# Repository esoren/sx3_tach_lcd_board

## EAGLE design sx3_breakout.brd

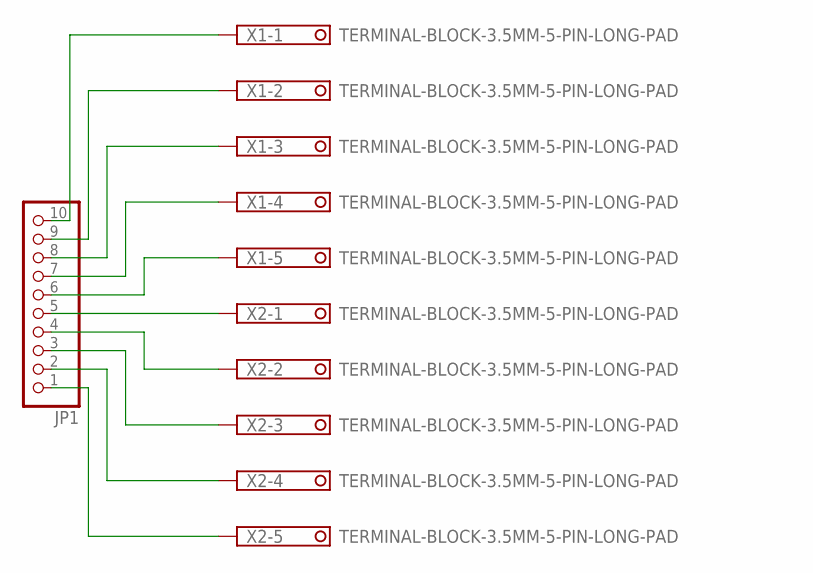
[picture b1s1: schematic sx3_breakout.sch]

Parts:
JP1: PINHD-1X10; 1X10
X1, X2: TERMINAL-BLOCK-3.5MM-5-PIN-LONG-PAD; TERMINAL-BLOCK-5-PIN-3.5MM-LONG-PAD

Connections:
unnamed: JP1.10, X1.1
unnamed: JP1.9, X1.2
unnamed: JP1.8, X1.3
unnamed: JP1.7, X1.4
unnamed: JP1.6, X1.5
unnamed: JP1.5, X2.1
unnamed: JP1.4, X2.2
unnamed: JP1.3, X2.3
unnamed: JP1.2, X2.4
unnamed: JP1.1, X2.5

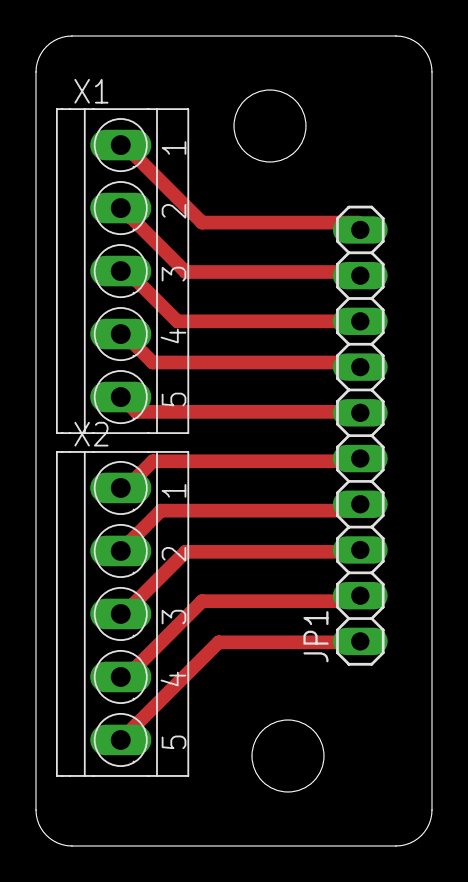
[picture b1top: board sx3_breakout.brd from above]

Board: 2 copper layers, 22.0 x 45.0 mm, 3 parts (0 on the bottom side), 10 nets.

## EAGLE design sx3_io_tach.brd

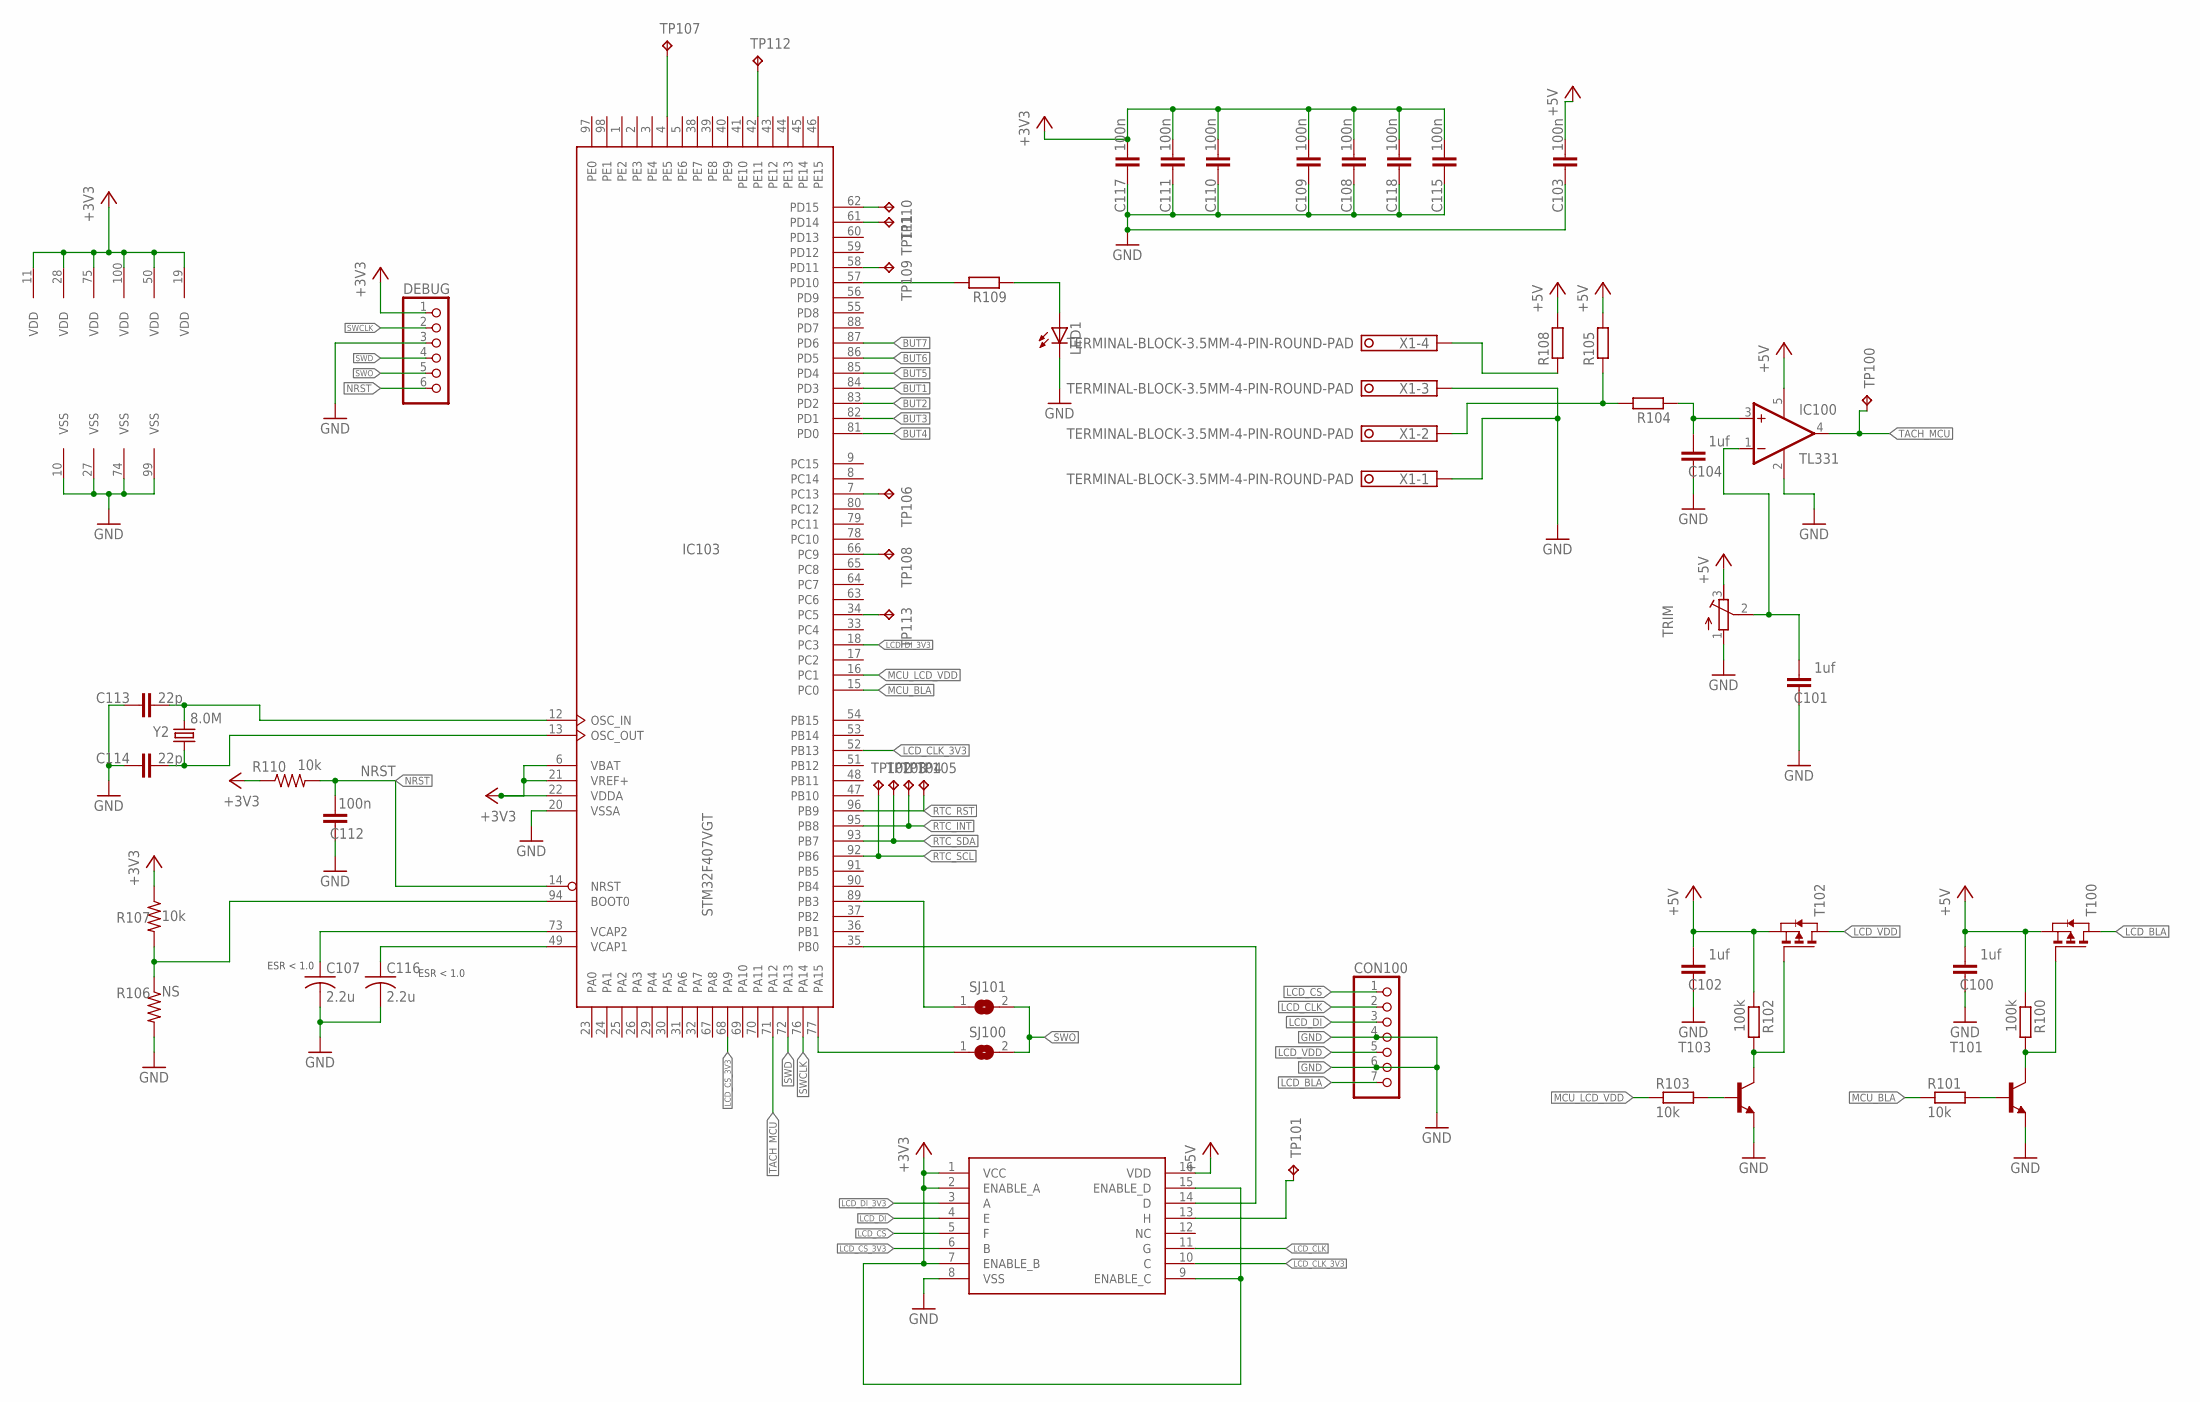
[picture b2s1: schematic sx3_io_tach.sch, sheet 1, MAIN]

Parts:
C100, C101, C102, C104: 1uf; C0603K
C103, C108, C109, C110, C111, C112, C115, C117, C118: 100n; C0603K
C107, C116: 2.2u; C1206
C113, C114: 22p; C0603K
CON100: PINHD-1X7; 1X07
DEBUG: PINHD-1X6; 1X06
IC100: TL331; DBV-R-PDSO-G5
IC103: STM32F407VGT; LQFP100
LED1: LED_ELD260; LED_LD260
R100, R102: 100k; R0603
R101, R103, R107, R110: 10k; R0603
R104, R105, R108, R109: R-EU_R0603; R0603
R106: NS; R0603
SJ100, SJ101: SJ
T100, T102: PMOSSOT23; SOT-23
T101, T103: BC817-NPN-SOT23-BEC; SOT23-BEC
TP100, TP101: TPB1,27; B1,27
TP102, TP103, TP104, TP105, TP106, TP107, TP108, TP109, TP110, TP111, TP112, TP113: TPTP17R; TP17R
TRIM: R-TRIMM3296W; RTRIM3296W
U$100: CD40109BPWR; TSSOP16
X1: TERMINAL-BLOCK-3.5MM-4-PIN-ROUND-PAD; TERMINAL-BLOCK-4-PIN-3.5MM-ROUND-PAD
Y2: 8.0M; HC49U-V

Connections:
+3V3: C108.2, C109.2, C110.2, C111.2, C115.2, C117.2, C118.2, DEBUG.1, IC103.6 (VBAT), IC103.11 (VDD), IC103.19 (VDD), IC103.21 (VREF+), IC103.22 (VDDA), IC103.28 (VDD), IC103.50 (VDD), IC103.75 (VDD), IC103.100 (VDD), R107.1, R110.1, U$100.1 (VCC), U$100.2 (ENABLE_A), U$100.7 (ENABLE_B), U$100.9 (ENABLE_C), U$100.15 (ENABLE_D); also elsewhere on the board
+5V: C100.2, C102.2, C103.2, IC100.5 (V+), R100.1, R102.1, R105.2, R108.2, T100.2 (S), T102.2 (S), TRIM.3 (E), U$100.16 (VDD); also elsewhere on the board
BOOT0: IC103.94 (BOOT0), R106.1, R107.2
BUT1: IC103.84 (PD3); also elsewhere on the board
BUT2: IC103.83 (PD2); also elsewhere on the board
BUT3: IC103.82 (PD1); also elsewhere on the board
BUT4: IC103.81 (PD0); also elsewhere on the board
BUT5: IC103.85 (PD4); also elsewhere on the board
BUT6: IC103.86 (PD5); also elsewhere on the board
BUT7: IC103.87 (PD6); also elsewhere on the board
GND: C100.1, C101.1, C102.1, C103.1, C104.1, C107.2, C108.1, C109.1, C110.1, C111.1, C112.1, C113.1, C114.1, C115.1, C116.2, C117.1, C118.1, CON100.4, CON100.6, DEBUG.3, IC100.2 (GND), IC103.10 (VSS), IC103.20 (VSSA), IC103.27 (VSS), IC103.74 (VSS), IC103.99 (VSS), LED1.K (C), R106.2, T101.E, T103.E, TRIM.1 (A), U$100.8 (VSS), X1.1, X1.3; also elsewhere on the board
LCD_BLA: CON100.7, T100.1 (D)
LCD_CLK: CON100.2, U$100.11 (G)
LCD_CLK_3V3: IC103.52 (PB13), U$100.10 (C)
LCD_CS: CON100.1, U$100.5 (F)
LCD_CS_3V3: IC103.68 (PA9), U$100.6 (B)
LCD_DI: CON100.3, U$100.4 (E)
LCD_DI_3V3: IC103.18 (PC3), U$100.3 (A)
LCD_VDD: CON100.5, T102.1 (D)
MCU_BLA: IC103.15 (PC0), R101.1
MCU_LCD_VDD: IC103.16 (PC1), R103.1
unnamed: C101.2, IC100.1 (-IN), TRIM.2 (S)
unnamed: IC103.57 (PD10), R109.2
unnamed: LED1.A, R109.1
unnamed: R101.2, T101.B
unnamed: R103.2, T103.B
unnamed: IC103.35 (PB0), U$100.14 (D)
unnamed: R102.2, T102.3 (G), T103.C
unnamed: TP101.TP, U$100.13 (H)
unnamed: R100.2, T100.3 (G), T101.C
unnamed: R108.1, X1.4
unnamed: IC103.4 (PE5), TP107.TP
unnamed: R104.2, R105.1, X1.2
unnamed: IC103.42 (PE11), TP112.TP
unnamed: C104.2, IC100.3 (+IN), R104.1
unnamed: IC103.66 (PC9), TP108.TP
unnamed: IC103.7 (PC13), TP106.TP
unnamed: IC103.34 (PC5), TP113.TP
unnamed: IC103.61 (PD14), TP111.TP
unnamed: IC103.62 (PD15), TP110.TP
unnamed: IC103.58 (PD11), TP109.TP
unnamed: IC103.89 (PB3), SJ101.1
unnamed: IC103.77 (PA15), SJ100.1
NRST: C112.2, DEBUG.6, IC103.14 (NRST), R110.2
OSC_IN: C113.2, IC103.12 (OSC_IN), Y2.2
OSC_OUT: C114.2, IC103.13 (OSC_OUT), Y2.1
RTC_INT: IC103.95 (PB8), TP104.TP
RTC_RST: IC103.96 (PB9), TP105.TP
RTC_SCL: IC103.92 (PB6), TP102.TP
RTC_SDA: IC103.93 (PB7), TP103.TP
SWCLK: DEBUG.2, IC103.76 (PA14)
SWD: DEBUG.4, IC103.72 (PA13)
SWO: DEBUG.5, SJ100.2, SJ101.2
TACH_MCU: IC100.4 (OUT), IC103.71 (PA12), TP100.TP; also elsewhere on the board
VCAP1: C116.1, IC103.49 (VCAP1)
VCAP2: C107.1, IC103.73 (VCAP2)

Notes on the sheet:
ESR < 1.0

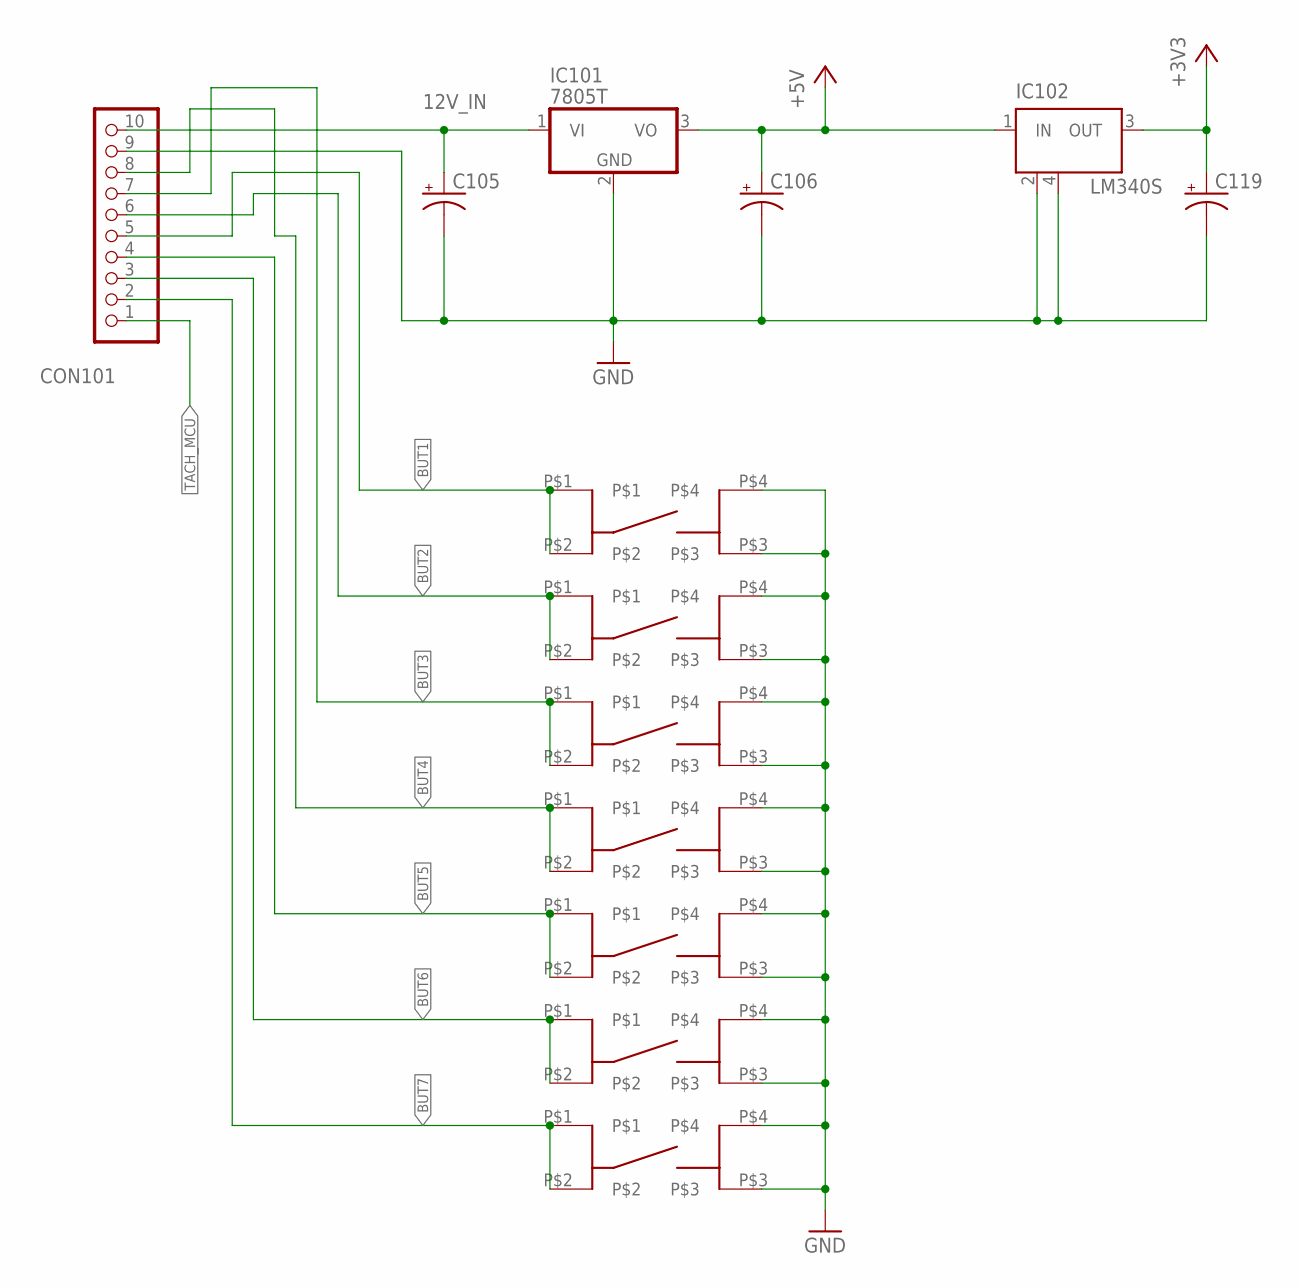
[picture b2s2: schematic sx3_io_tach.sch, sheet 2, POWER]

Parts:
C105, C106, C119: CPOL-USE2,5-6E; E2,5-6E
CON101: PINHD-1X10; 1X10
IC101: 7805T; TO220H
IC102: LM340S; SOT223
U$1, U$2, U$3, U$4, U$5, U$6, U$7: TE_2-1825910; TE_2-1825910-7

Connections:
12V_IN: C105.+, CON101.10, IC101.1 (VI)
+3V3: C119.+, IC102.3 (OUT); also elsewhere on the board
+5V: C106.+, IC101.3 (VO), IC102.1 (IN); also elsewhere on the board
BUT1: CON101.5, U$7.P$1, U$7.P$2; also elsewhere on the board
BUT2: CON101.6, U$5.P$1, U$5.P$2; also elsewhere on the board
BUT3: CON101.7, U$3.P$1, U$3.P$2; also elsewhere on the board
BUT4: CON101.8, U$1.P$1, U$1.P$2; also elsewhere on the board
BUT5: CON101.4, U$2.P$1, U$2.P$2; also elsewhere on the board
BUT6: CON101.3, U$4.P$1, U$4.P$2; also elsewhere on the board
BUT7: CON101.2, U$6.P$1, U$6.P$2; also elsewhere on the board
GND: C105.-, C106.-, C119.-, CON101.9, IC101.2 (GND), IC102.2 (GND), IC102.4 (GND), U$1.P$3, U$1.P$4, U$2.P$3, U$2.P$4, U$3.P$3, U$3.P$4, U$4.P$3, U$4.P$4, U$5.P$3, U$5.P$4, U$6.P$3, U$6.P$4, U$7.P$3, U$7.P$4; also elsewhere on the board
TACH_MCU: CON101.1; also elsewhere on the board

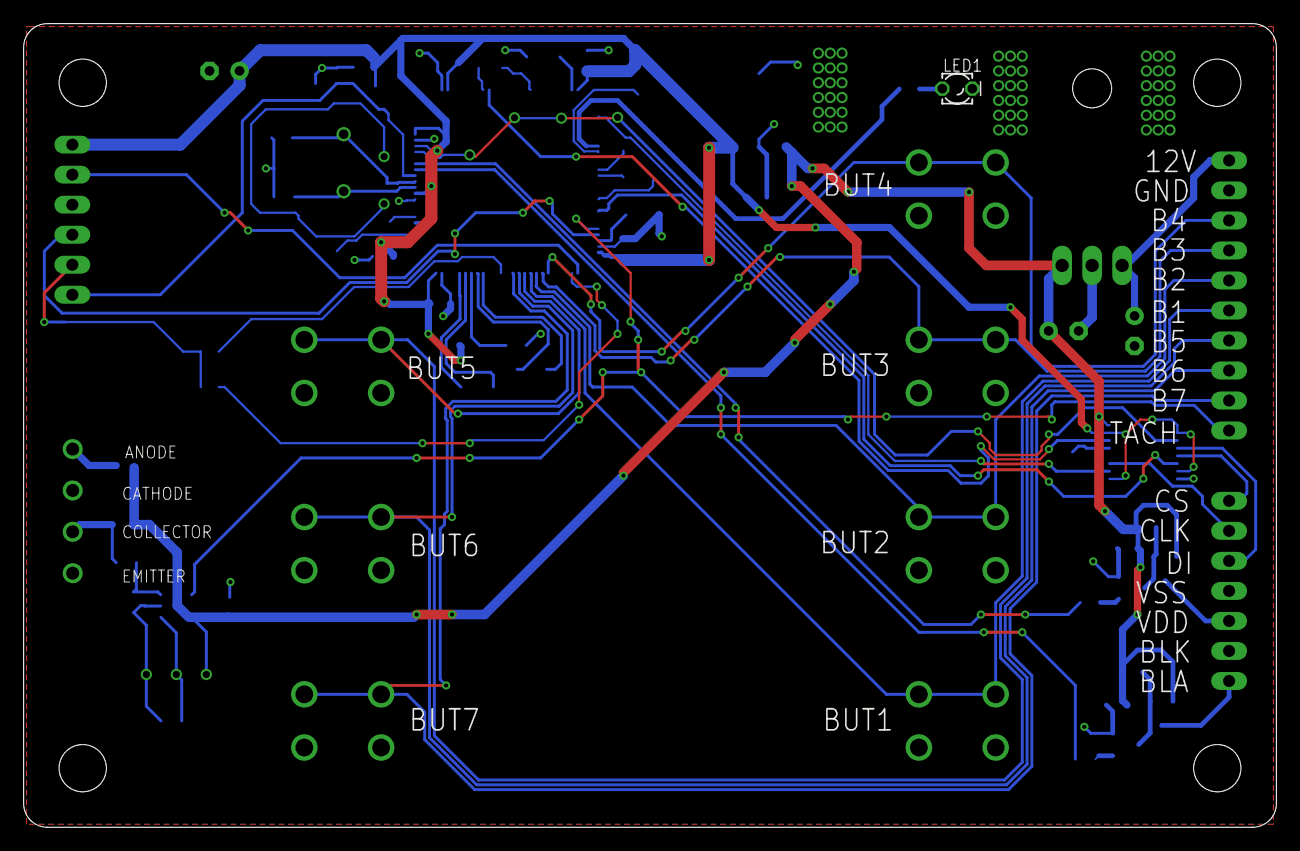
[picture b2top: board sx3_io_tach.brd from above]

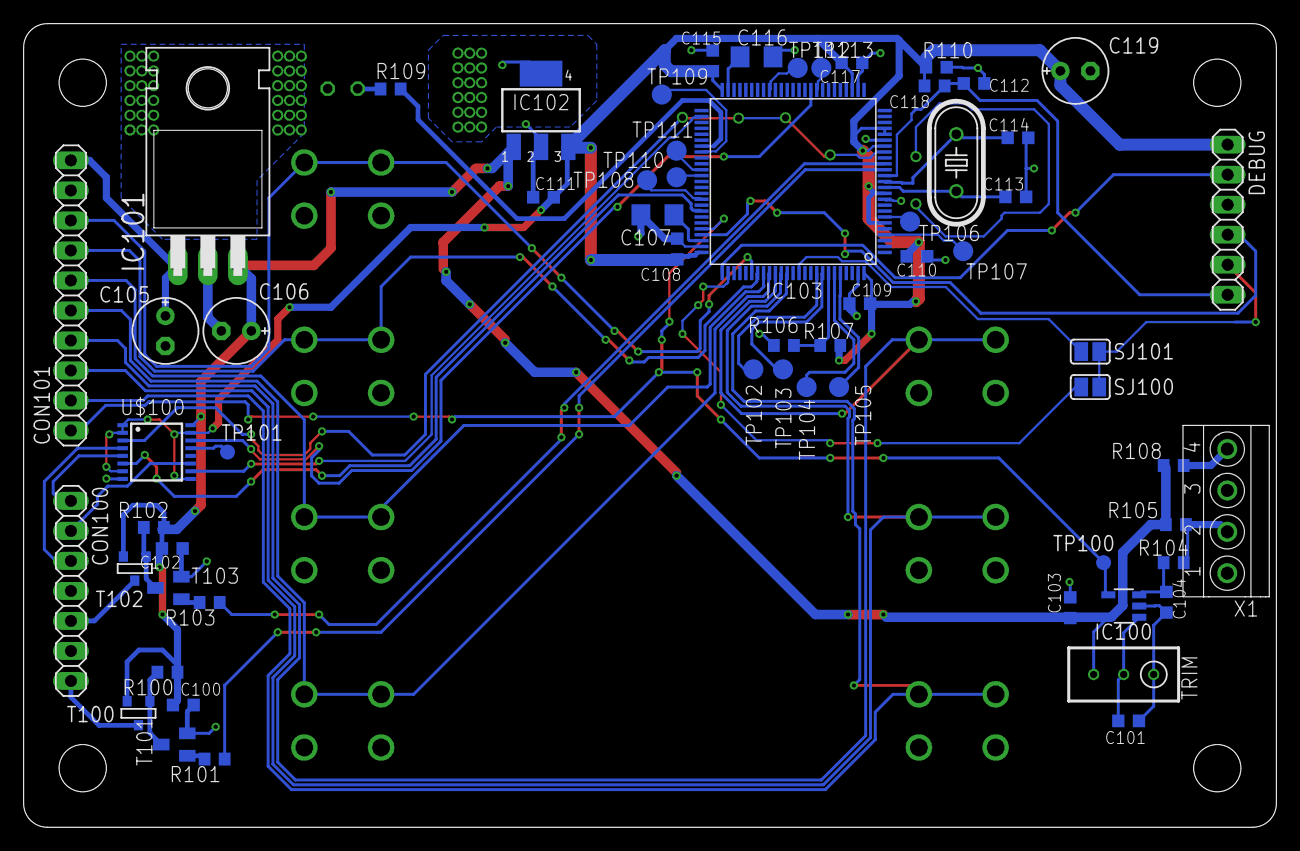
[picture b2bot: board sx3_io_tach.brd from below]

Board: 2 copper layers, 106.0 x 68.0 mm, 70 parts (62 on the bottom side), 57 nets.

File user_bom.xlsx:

Designators | Digikey Part # | Qty | Description
R100 R102 | YAG1235CT-ND | 2 | 100k resistor 0603
T101 T1023 | MMBT3904TPMSCT-ND | 2 | sot23 npn transistor
LED1 | 732-5008-ND | 1 | through hole LED
CON101 | WM4208-ND | 1 | 1x10 0.1" pin header
CON100 | WM4205-ND | 1 | 1x7 0.1" pin header
DEBUG |  |  | 1x6 0.1" pin header
T100, T102 | SSM3J328RLFCT-ND | 2 | sot23 pmos
R108, R109 | A130089CT-ND | 2 | 470 ohm 0603 resistor
R104 | 311-0.0JRCT-ND | 1 | 0 ohm 0603 resistor
R105, R106 | nostuff | 2 | nostuff
TRIM | 490-2875-ND | 1 | 10k trimpot
C103, C108, C109, C110, C111, C112, C115, C117, C118 | 490-4767-1-ND | 9 | 100n 0603 cap
R101, R103 R107, R110 | P10KGCT-ND | 4 | 10k 0603 resistor
C100, C101, C102, C104 | 311-1445-1-ND | 4 | 1uf 0603 resistor
C107, C116 | 445-8221-1-ND | 2 | 2.2u 1206 ESR<1
C113, C114 | 709-1143-1-ND | 2 | 20p 0603 capacitor
IC101 | 296-47192-ND | 1 | 7805 regulator
Y2 | 887-1233-ND | 1 | 8M crystal HC49U
U$100 | 296-12163-1-ND | 1 | CD40109BPWR level shifter
IC102 | MCP1824ST-3302E/DBDKR-ND | 1 | 3v3 regulator sot-23
IC103 | 497-17438-ND | 1 | STM32F407VGT (LQFP100)
X1 | 277-5744-ND | 1 | 1x4 3.5mm termional block
U$1 U$2 U$3 U$4 U$5 U$6 U$7 | 450-1642-ND | 7 | Button: TE_2-1825910
IC100 | 296-10168-1-ND | 1 | TL331
EXTERNAL | 365-1900-ND | 1 | Sensor (OPB70AWZ)
1-time:
497-17442-ND | 1

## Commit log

2019-12-01 Initial Commit after first prototype

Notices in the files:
parts and their libraries:
SparkFun-FreqCtrl: Licensing: Creative Commons ShareAlike 4.0 International - https://creativecommons.org/licenses/by-sa/4.0
